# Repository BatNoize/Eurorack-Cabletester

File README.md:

# Arduino 10/16 pin Eurorack IDC Power Cable Tester

## History
1. Forked from https://github.com/tomarus/cabletester with slight modifications to circuit and software (mainly order of connections), and with PCB layout added.
2. This is froked from https://gitlab.com/rsholmes/cabletester. 

## Changes
- Modified to SMD resistors.
- The single capacitor C1 is still a THT capacitor. I overlooked that. However, an 0805 SMD component can easily be used.
- Add M3 mounting holes.
- An OpenSCAD drawing for a 3D enclosure to protect the underside of the circuit boards has been added. (The OpenSCAD code is not beautiful but it's functional)

## Features
It only tests (max) 8 wires because of how they're wired in eurorack.
It can detect shorted cables or faulty/unconnected wires.

This project uses a 128x64 OLED I2C display module with four interface pins: GND, +12V, SCL, and SDA. It is a monochrome display although it is available in a version with a yellow and blue overlay as seen in the photos. Note that the OLED pinout sometimes is GND-VCC-SCL-SDA and sometimes VCC-GND-SCL-SDA. The initial run of boards assumed the latter pinout; the present design has footprints for both.
These modules are available from the "usual suspects" on Amazon, eBay, AliExpress, etc. I have one of these (GND-VCC-SCL-SDA) and one of these (VCC-GND-SCL-SDA). They do not seem to be available from any established vendors like Mouser, DigiKey, Tayda, Adafruit, or SparkFun. Please make sure you have a source for the display before proceeding with this project!
Code uses these libraries:

- https://github.com/adafruit/Adafruit_SSD1306
- https://github.com/adafruit/Adafruit-GFX-Library

## Original Schematic

## PCB

## Case

Here is the preview openSCAD Case for the cabletester.
You need 4x M3x10mm countersunk screws and 4x M3 nuts.

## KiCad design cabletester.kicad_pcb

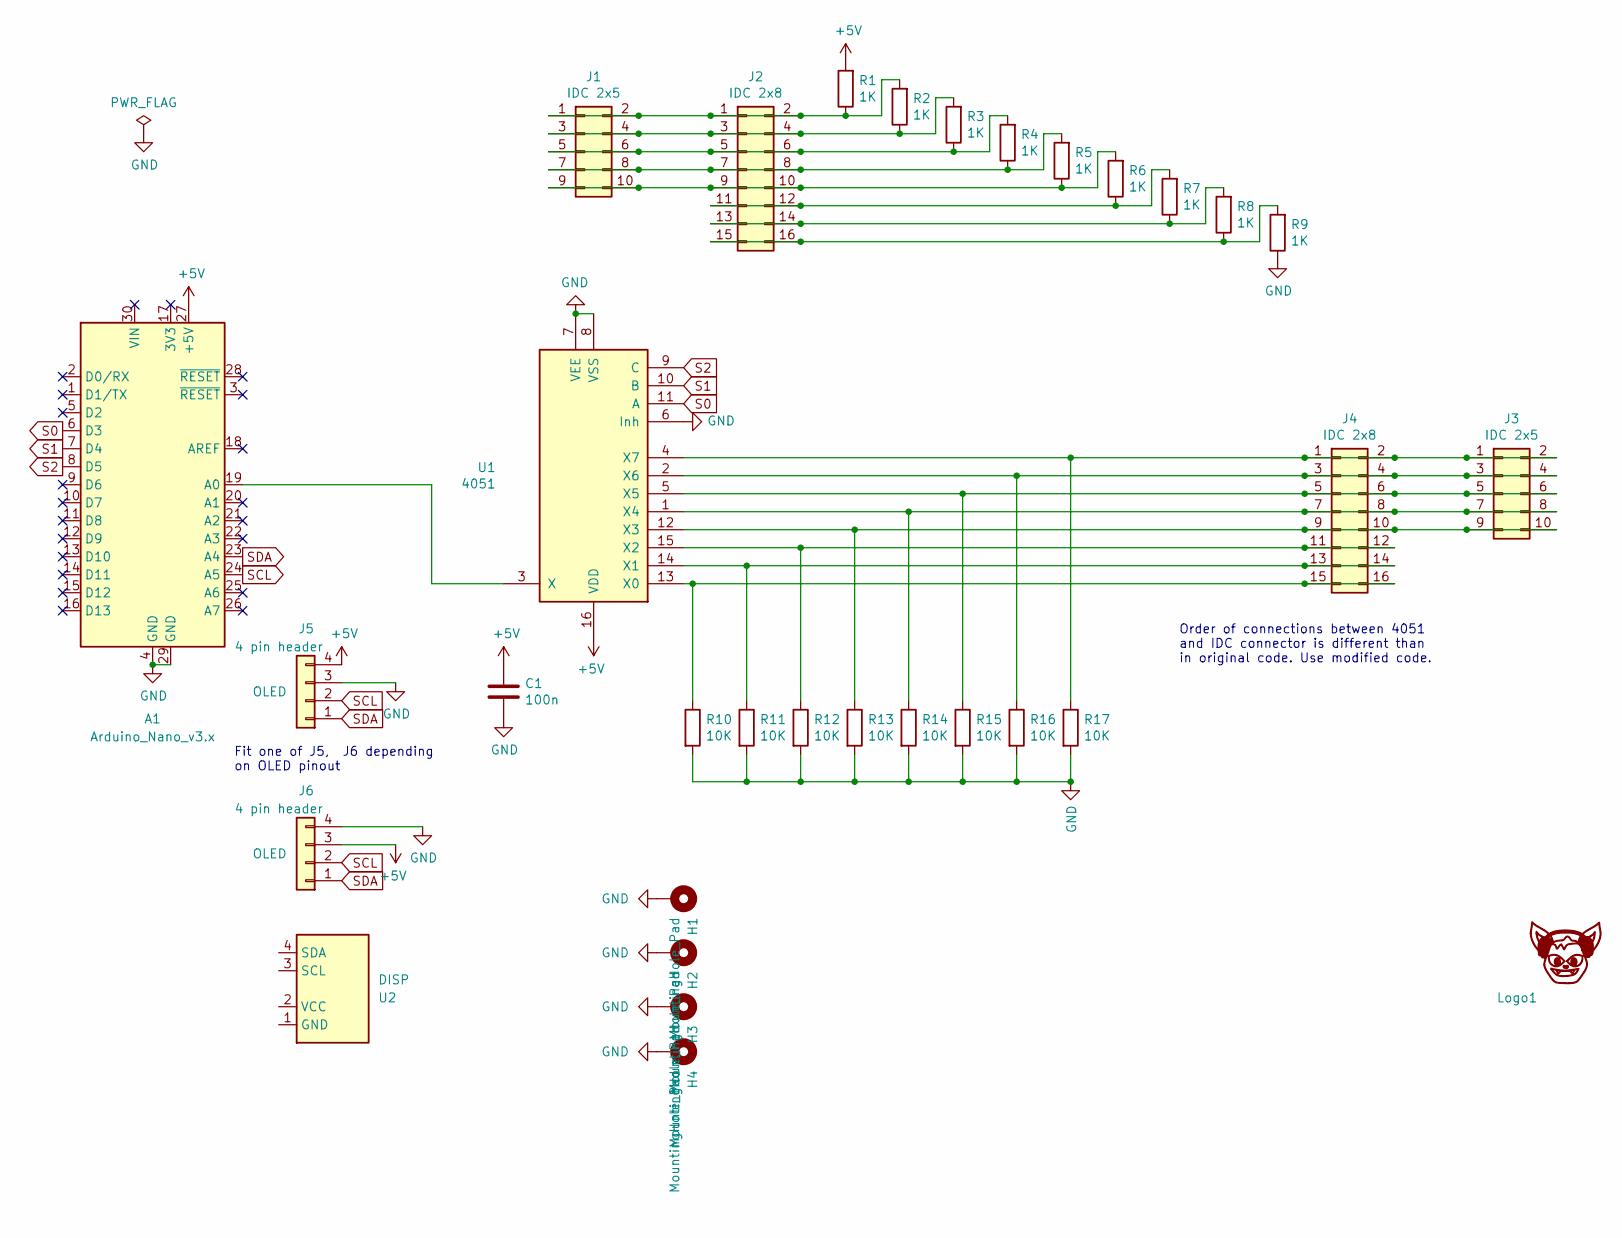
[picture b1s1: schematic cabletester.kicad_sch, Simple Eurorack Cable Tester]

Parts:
A1: Arduino_Nano_v3.x; Arduino_Nano
C1: 100n; C_Disc_D3.0mm_W1.6mm_P2.50mm
H1, H2, H3, H4: MountingHole_Pad; MountingHole_3.2mm_M3_Pad
J1, J3: IDC 2x5; Power_Header
J2, J4: IDC 2x8; IDC-Header_2x08_P2.54mm_Vertical
J5, J6: 4 pin header; PinSocket_1x04_P2.54mm_Vertical
Logo1: LOGO; Logo_10mm_SS
R1, R2, R3, R4, R5, R6, R7, R8, R9: 1K; R_0805_2012Metric_Pad1.20x1.40mm_HandSolder
R10, R11, R12, R13, R14, R15, R16, R17: 10K; R_0805_2012Metric_Pad1.20x1.40mm_HandSolder
U1: 4051; DIP-16_W7.62mm_Socket_LongPads
U2: DISP; OLED_MC096_128x64 i2c_(Only Display No THT)

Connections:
+5V: A1.27 (+5V), C1.1, J5.4, J6.3, R1.2, U1.16 (VDD)
GND: A1.4 (GND), A1.29 (GND), C1.2, H1.1, H2.1, H3.1, H4.1, J5.3, J6.4, R9.1, R10.2, R11.2, R12.2, R13.2, R14.2, R15.2, R16.2, R17.2, U1.6 (Inh), U1.7 (VEE), U1.8 (VSS)
unnamed: A1.19 (A0), U1.3 (X)
unnamed: J1.1, J1.2, J2.1, J2.2, R1.1, R2.2
unnamed: J1.3, J1.4, J2.3, J2.4, R2.1, R3.2
unnamed: J1.5, J1.6, J2.5, J2.6, R3.1, R4.2
unnamed: J1.7, J1.8, J2.7, J2.8, R4.1, R5.2
unnamed: J1.9, J1.10, J2.9, J2.10, R5.1, R6.2
unnamed: J2.11, J2.12, R6.1, R7.2
unnamed: J2.13, J2.14, R7.1, R8.2
unnamed: J2.15, J2.16, R8.1, R9.2
unnamed: J3.1, J3.2, J4.1, J4.2, R17.1, U1.4 (X7)
unnamed: J3.3, J3.4, J4.3, J4.4, R16.1, U1.2 (X6)
unnamed: J3.5, J3.6, J4.5, J4.6, R15.1, U1.5 (X5)
unnamed: J3.7, J3.8, J4.7, J4.8, R14.1, U1.1 (X4)
unnamed: J3.9, J3.10, J4.9, J4.10, R13.1, U1.12 (X3)
unnamed: J4.11, J4.12, R12.1, U1.15 (X2)
unnamed: J4.13, J4.14, R11.1, U1.14 (X1)
unnamed: J4.15, J4.16, R10.1, U1.13 (X0)
S0: A1.6 (D3), U1.11 (A)
S1: A1.7 (D4), U1.10 (B)
S2: A1.8 (D5), U1.9 (C)
SCL: A1.24 (A5), J5.2, J6.2
SDA: A1.23 (A4), J5.1, J6.1

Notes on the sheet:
Order of connections between 4051 and IDC connector is different than in original code. Use modified code.
Fit one of J5, J6 depending on OLED pinout

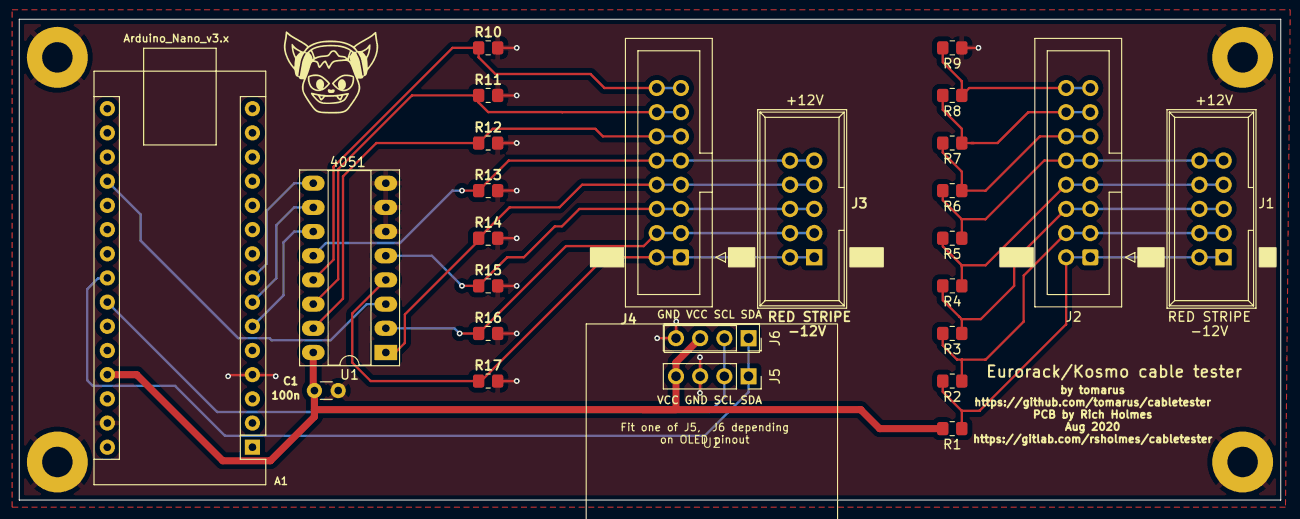
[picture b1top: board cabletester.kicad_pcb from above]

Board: 2 copper layers, 132.5 x 50.5 mm, 32 parts (0 on the bottom side), 24 nets.

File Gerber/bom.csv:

Designator,Footprint,Quantity,Value,LCSC Part #
A1,Arduino_Nano,1,Arduino_Nano_v3.x,
C1,0805,1,100n,
"J1, J3",Power_Header,2,IDC 2x5,
"J2, J4",IDC-Header_2x08_P2.54mm_Vertical,2,IDC 2x8,
"J5, J6",PinSocket_1x04_P2.54mm_Vertical,2,4 pin header,
"R1, R2, R3, R4, R5, R6, R7, R8, R9",0805,9,1K,
"R10, R11, R12, R13, R14, R15, R16, R17",0805,8,10K,
U1,DIP-16_W7.62mm_Socket_LongPads,1,4051,
U2,OLED_MC096_128x64 i2c_(Only Display No THT),1,DISP,

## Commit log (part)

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2025-11-08 Create LICENSE
2025-11-08 init
